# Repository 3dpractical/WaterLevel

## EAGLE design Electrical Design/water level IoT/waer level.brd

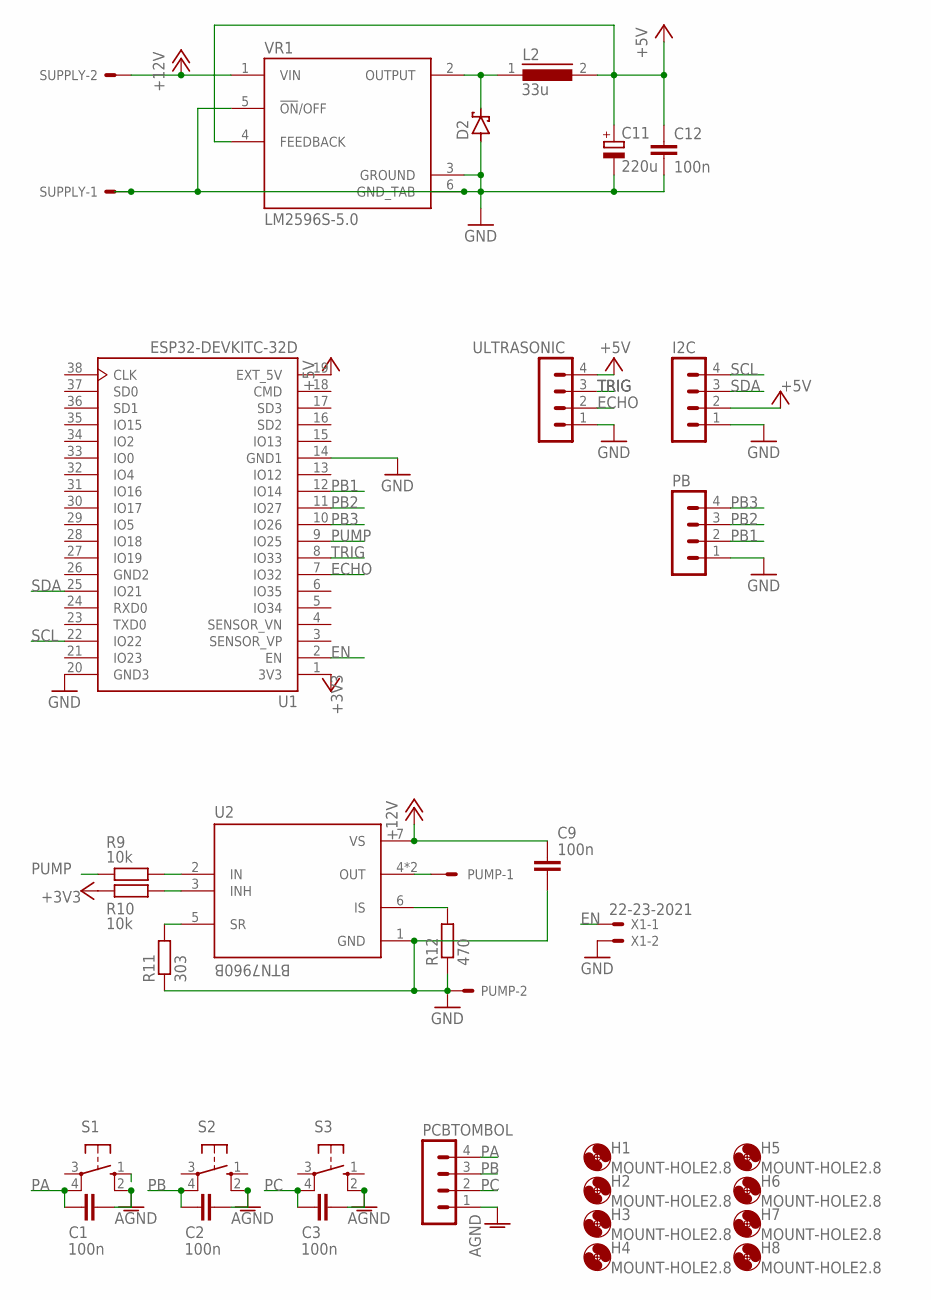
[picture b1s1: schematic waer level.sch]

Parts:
C1, C2, C3, C9, C12: 100n; C0805
C11: 220u; 153CLV-0605
D2: SCHOTTKY-DIODESMD; SMB
H1, H2, H3, H4, H5, H6, H7, H8: MOUNT-HOLE2.8; 2,8
I2C: MA04-1
L2: 33u; DR125
PB: MA04-1
PCBTOMBOL: MA04-1
PUMP: KK-156-2
R9, R10: 10k; R0805
R11: 303; R0805
R12: 470; R0805
S1, S2, S3: 40-XX; B3F-40XX
SUPPLY: KK-156-2
U1: ESP32-DEVKITC-32D; MODULE_ESP32-DEVKITC-32D
U2: BTN7960B; IC_BTN7960B
ULTRASONIC: MA04-1
VR1: LM2596S-5.0; TO170P1524X483-6N
X1: 22-23-2021

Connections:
+3V3: R10.1, U1.1 (3V3)
+5V: C11.+, C12.1, I2C.2, L2.2, U1.19 (EXT_5V), ULTRASONIC.4, VR1.4 (FEEDBACK)
+12V: C9.1, SUPPLY.2, U2.7 (VS), VR1.1 (VIN)
AGND: C1.2, C2.2, C3.2, PCBTOMBOL.1, S1.2 (S1), S2.2 (S1), S3.2 (S1)
ECHO: U1.7 (IO32), ULTRASONIC.2
EN: U1.2 (EN), X1.1
GND: C9.2, C11.-, C12.2, D2.A, I2C.1, PB.1, PUMP.2, R11.1, R12.1, SUPPLY.1, U1.14 (GND1), U1.20 (GND3), U2.1 (GND), ULTRASONIC.1, VR1.3 (GROUND), VR1.5 (!ON!/OFF), VR1.6 (GND_TAB), X1.2
GND2: U1.26 (GND2)
unnamed: R9.2, U2.2 (IN)
unnamed: R10.2, U2.3 (INH)
unnamed: D2.C, L2.1, VR1.2 (OUTPUT)
unnamed: R11.2, U2.5 (SR)
unnamed: R12.2, U2.6 (IS)
unnamed: PUMP.1, U2.4 (OUT), U2.8 (OUT)
PA: C1.1, PCBTOMBOL.4, S1.4 (P1)
PB: C2.1, PCBTOMBOL.3, S2.4 (P1)
PB1: PB.2, U1.12 (IO14)
PB2: PB.3, U1.11 (IO27)
PB3: PB.4, U1.10 (IO26)
PC: C3.1, PCBTOMBOL.2, S3.4 (P1)
PUMP: R9.1, U1.9 (IO25)
SCL: I2C.4, U1.22 (IO22)
SDA: I2C.3, U1.25 (IO21)
TRIG: U1.8 (IO33), ULTRASONIC.3

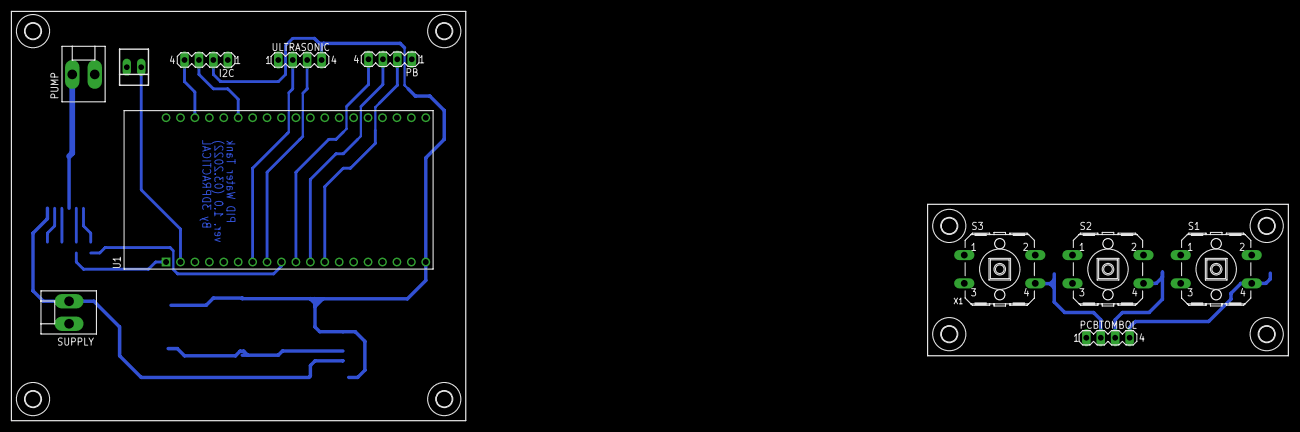
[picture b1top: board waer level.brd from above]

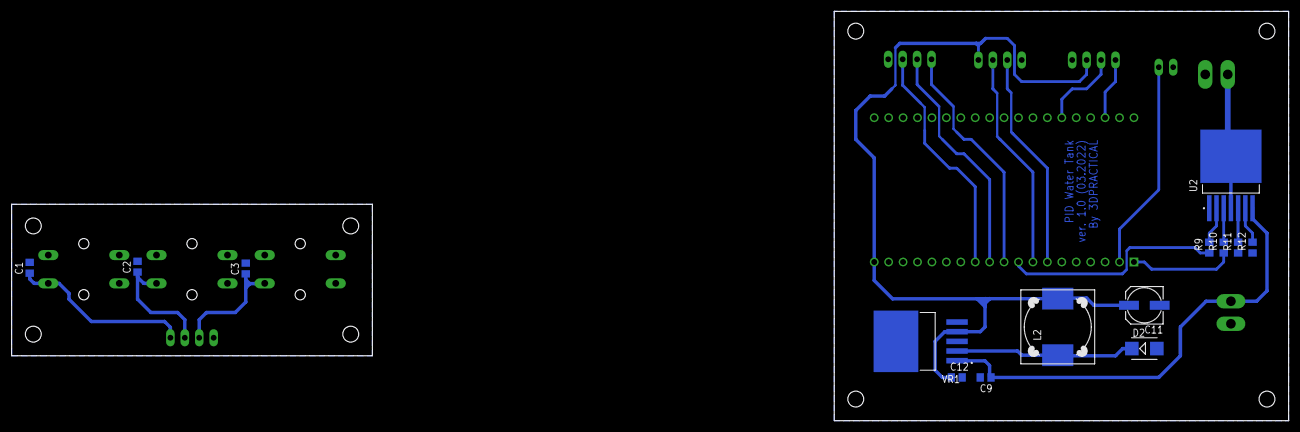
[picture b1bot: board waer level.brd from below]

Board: 2 copper layers, 224.7 x 72.0 mm, 33 parts (14 on the bottom side), 23 nets.
